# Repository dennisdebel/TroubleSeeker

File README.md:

# TroubleSeeker
Electromagnetic Radiation detector, based on the [Elektrosluch 3 by LOM Audio](https://store.lom.audio/products/elektrosluch-3?variant=4542168268832) re-designed for workshops (cost optimisation and ease of soldering). Perfboard variant can be found [here](https://makezine.com/projects/weekend-project-sample-weird-sounds-electromagnetic-fields)

Component values are non crucial.

Assembly tutorial [here](https://youtu.be/3JtvDqBiOzs)

First debuted at the TroubleMaker Shenzhen Reboot June 2024 Huaqiangbei.

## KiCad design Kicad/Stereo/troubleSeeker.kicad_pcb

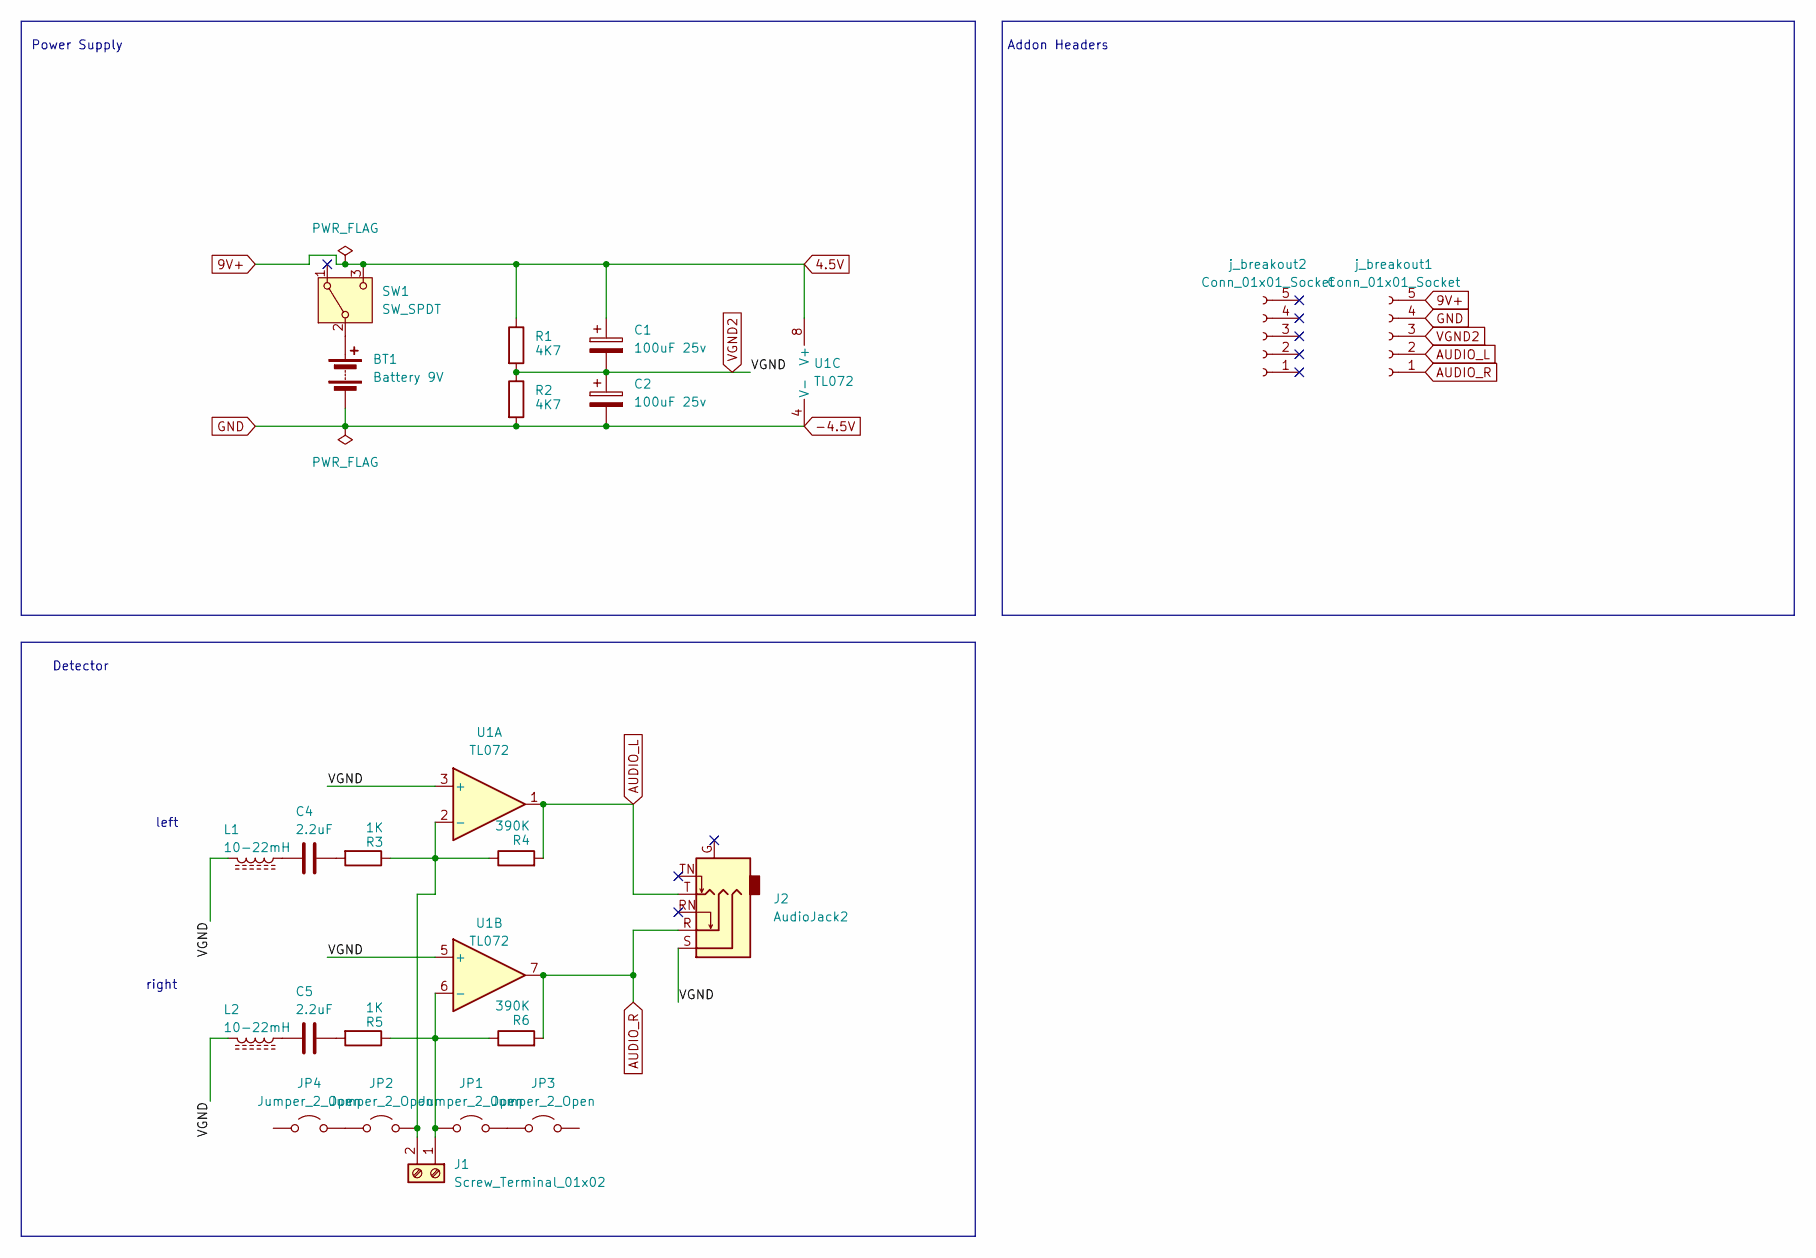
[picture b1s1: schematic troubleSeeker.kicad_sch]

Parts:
BT1: Battery 9V; BatteryHolder_Eagle_12BH611-GR
C1, C2: 100uF 25v; CP_Radial_D8.0mm_P5.00mm
C4, C5: 2.2uF; C_Rect_L7.2mm_W3.0mm_P5.00mm_FKS2_FKP2_MKS2_MKP2
J1: Screw_Terminal_01x02; TerminalBlock_MaiXu_MX126-5.0-02P_1x02_P5.00mm
J2: AudioJack2; Jack_3.5mm_CUI_SJ1-3525N_Horizontal
JP1, JP2, JP3, JP4: Jumper_2_Open; SolderJumper-2_P1.3mm_Open_RoundedPad1.0x1.5mm
L1, L2: 10-22mH; L_Radial_D8.7mm_P5.00mm_Fastron_07HCP
R1, R2: 4K7; R_Axial_DIN0207_L6.3mm_D2.5mm_P10.16mm_Horizontal
R3, R5: 1K; R_Axial_DIN0207_L6.3mm_D2.5mm_P10.16mm_Horizontal
R4, R6: 390K; R_Axial_DIN0207_L6.3mm_D2.5mm_P10.16mm_Horizontal
SW1: SW_SPDT; SW_Slide_SPDT_Angled_CK_OS102011MA1Q
U1: TL072; DIP-8_W7.62mm_Socket_LongPads
j_breakout1, j_breakout2: Conn_01x01_Socket; PinHeader_1x05_P2.54mm_Vertical

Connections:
4.5V: C1.1, R1.1, SW1.3 (C), U1.8 (V+), j_breakout1.5
-4.5V: BT1.2 (-), C2.2, R2.2, U1.4 (V-), j_breakout1.4
AUDIO_L: J2.T, R4.2, U1.1, j_breakout1.2
AUDIO_R: J2.R, R6.2, U1.7, j_breakout1.1
unnamed: BT1.1 (+), SW1.2 (B)
unnamed: C4.1, R3.2
unnamed: C4.2, L1.1
unnamed: C5.1, R5.2
unnamed: C5.2, L2.1
unnamed: J1.1, JP1.1 (A), R5.1, R6.1, U1.6 (-)
unnamed: J1.2, JP2.2 (B), R3.1, R4.1, U1.2 (-)
unnamed: JP1.2 (B), JP3.1 (A)
unnamed: JP2.1 (A), JP4.2 (B)
VGND2: C1.2, C2.1, J2.S, L1.2, L2.2, R1.2, R2.1, U1.3 (+), U1.5 (+), j_breakout1.3

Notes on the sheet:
Detector
Power Supply
Addon Headers
right
left

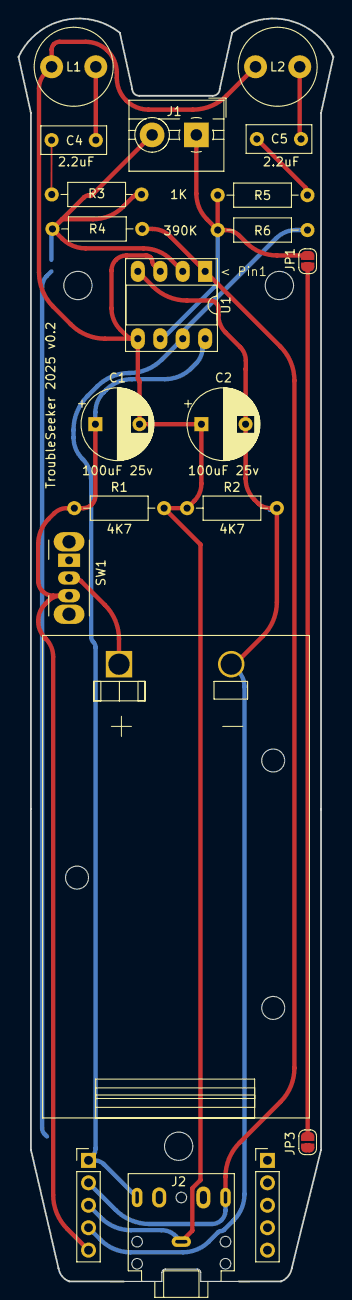
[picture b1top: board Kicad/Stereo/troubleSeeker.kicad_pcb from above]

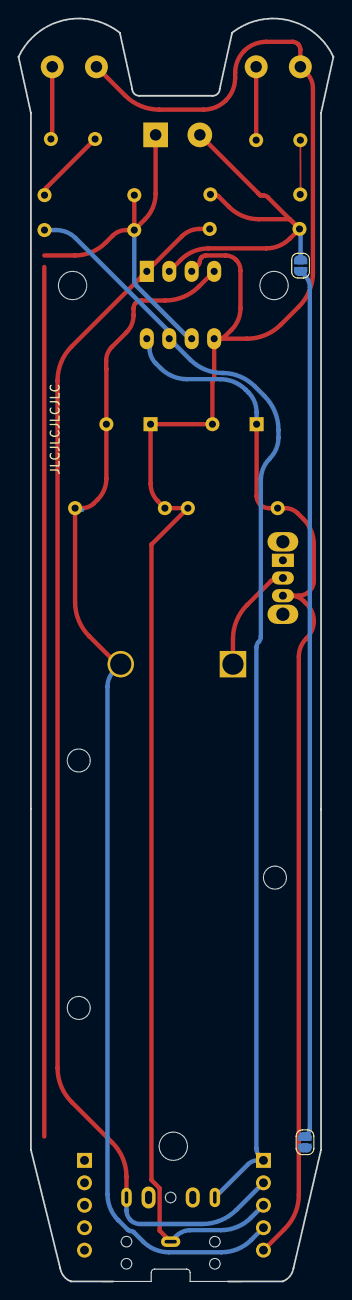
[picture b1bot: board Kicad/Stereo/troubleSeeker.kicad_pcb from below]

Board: 2 copper layers, 35.6 x 142.9 mm, 23 parts (3 on the bottom side), 14 nets.

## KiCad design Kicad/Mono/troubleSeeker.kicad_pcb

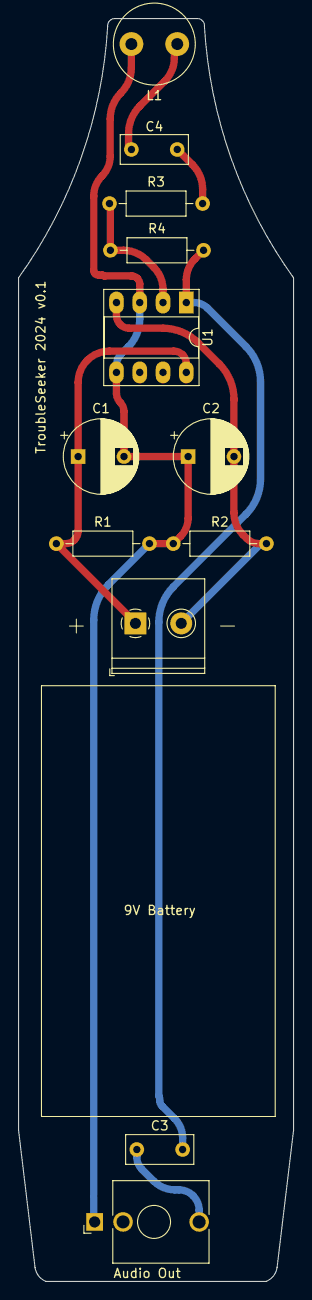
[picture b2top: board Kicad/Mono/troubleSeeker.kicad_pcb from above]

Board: 2 copper layers, 30.0 x 137.8 mm, 12 parts (0 on the bottom side), 8 nets.

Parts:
9V Battery: Battery 9V; TerminalBlock_Philmore_TB132_1x02_P5.00mm_Horizontal
Audio Out: AudioJack2; Jack_3.5mm_QingPu_WQP-PJ398SM_Vertical_CircularHoles
C1, C2: 100uF 25v; CP_Radial_D8.0mm_P5.00mm
C3, C4: 2.2uF; C_Rect_L7.2mm_W3.0mm_P5.00mm_FKS2_FKP2_MKS2_MKP2
L1: 10-22mH; L_Radial_D8.7mm_P5.00mm_Fastron_07HCP
R1, R2: 4K7; R_Axial_DIN0207_L6.3mm_D2.5mm_P10.16mm_Horizontal
R3: 1K; R_Axial_DIN0207_L6.3mm_D2.5mm_P10.16mm_Horizontal
R4: 390K; R_Axial_DIN0207_L6.3mm_D2.5mm_P10.16mm_Horizontal
U1: TL072; DIP-8_W7.62mm_Socket_LongPads

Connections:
/VGND: Audio Out.S, C1.2, C2.1, L1.2, R1.2, R2.1, U1.3 (+), U1.5 (+)
unnamed: 9V Battery.1 (+), C1.1, R1.1, U1.8 (V+)
unnamed: 9V Battery.2 (-), C2.2, R2.2, U1.4 (V-)
unnamed: Audio Out.T, C3.1
unnamed: C3.2, R4.2, U1.1
unnamed: C4.1, R3.2
unnamed: C4.2, L1.1
unnamed: R3.1, R4.1, U1.2 (-)

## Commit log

2024-07-11 Added production files
2024-07-11 Added Kicad files
2024-07-11 Added Image
2024-07-12 Update README.md
    Added tutorial
2025-02-17 Added Stereo Design
2025-02-17 Replaced switch
2025-02-18 added gerbers
2025-02-18 minor adjustments
